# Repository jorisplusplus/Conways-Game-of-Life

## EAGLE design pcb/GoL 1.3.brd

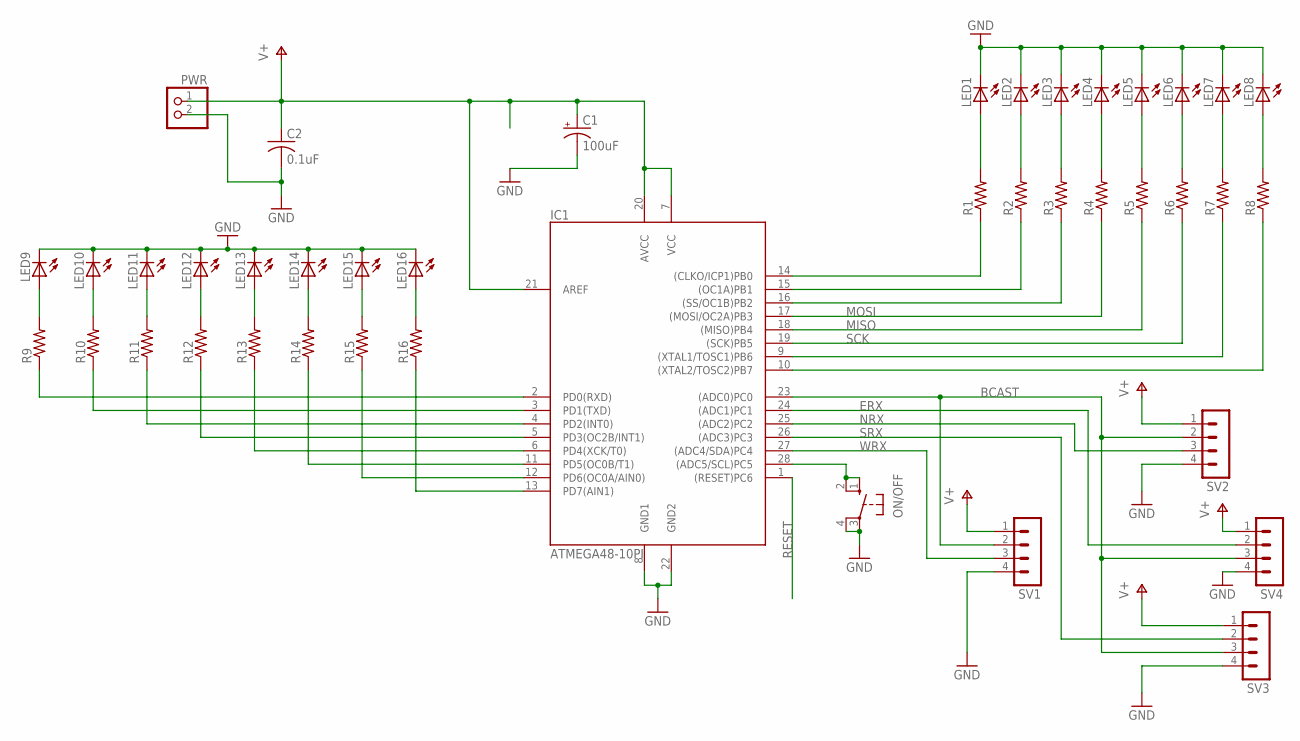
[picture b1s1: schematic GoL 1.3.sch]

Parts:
C1: 100uF; E2,5-6
C2: 0.1uF; C025-025X050
IC1: ATMEGA48-10PI; DIL28-3
LED1, LED2, LED3, LED4, LED5, LED6, LED7, LED8, LED9, LED10, LED11, LED12, LED13, LED14, LED15, LED16: LED5MMEZ; LED5MM-EZ
ON/OFF: 10-XX; B3F-10XX
PWR: PINHD-1X2; 1X02
R1, R2, R3, R4, R5, R6, R7, R8, R9, R10, R11, R12, R13, R14, R15, R16: R-US_0207/10; 0207/10
SV1, SV2, SV3, SV4: MA04-1

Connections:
BCAST: IC1.23 ((ADC0)PC0), SV1.2, SV2.2, SV3.3, SV4.3
ERX: IC1.24 ((ADC1)PC1), SV4.2
GND: C1.-, C2.2, IC1.8 (GND1), IC1.22 (GND2), LED1.K (C), LED2.K (C), LED3.K (C), LED4.K (C), LED5.K (C), LED6.K (C), LED7.K (C), LED8.K (C), LED9.K (C), LED10.K (C), LED11.K (C), LED12.K (C), LED13.K (C), LED14.K (C), LED15.K (C), LED16.K (C), ON/OFF.3, ON/OFF.4 (P1), PWR.2, SV1.4, SV2.4, SV3.4, SV4.4
MISO: IC1.18 ((MISO)PB4), R5.1
MOSI: IC1.17 ((MOSI/OC2A)PB3), R4.1
unnamed: LED1.A, R1.2
unnamed: LED2.A, R2.2
unnamed: LED3.A, R3.2
unnamed: LED4.A, R4.2
unnamed: LED5.A, R5.2
unnamed: LED6.A, R6.2
unnamed: LED7.A, R7.2
unnamed: LED8.A, R8.2
unnamed: LED9.A, R9.2
unnamed: LED10.A, R10.2
unnamed: LED11.A, R11.2
unnamed: LED12.A, R12.2
unnamed: LED13.A, R13.2
unnamed: LED14.A, R14.2
unnamed: LED15.A, R15.2
unnamed: LED16.A, R16.2
unnamed: IC1.13 (PD7(AIN1)), R16.1
unnamed: IC1.12 (PD6(OC0A/AIN0)), R15.1
unnamed: IC1.11 (PD5(OC0B/T1)), R14.1
unnamed: IC1.6 (PD4(XCK/T0)), R13.1
unnamed: IC1.5 (PD3(OC2B/INT1)), R12.1
unnamed: IC1.4 (PD2(INT0)), R11.1
unnamed: IC1.3 (PD1(TXD)), R10.1
unnamed: IC1.2 (PD0(RXD)), R9.1
unnamed: IC1.28 ((ADC5/SCL)PC5), ON/OFF.1 (S), ON/OFF.2 (S1)
unnamed: IC1.14 ((CLKO/ICP1)PB0), R1.1
unnamed: IC1.15 ((OC1A)PB1), R2.1
unnamed: IC1.16 ((SS/OC1B)PB2), R3.1
unnamed: IC1.9 ((XTAL1/TOSC1)PB6), R7.1
unnamed: IC1.10 ((XTAL2/TOSC2)PB7), R8.1
NRX: IC1.25 ((ADC2)PC2), SV2.3
RESET: IC1.1 ((RESET)PC6)
SCK: IC1.19 ((SCK)PB5), R6.1
SRX: IC1.26 ((ADC3)PC3), SV3.2
V+: C1.+, C2.1, IC1.7 (VCC), IC1.20 (AVCC), IC1.21 (AREF), PWR.1, SV1.1, SV2.1, SV3.1, SV4.1
WRX: IC1.27 ((ADC4/SDA)PC4), SV1.3

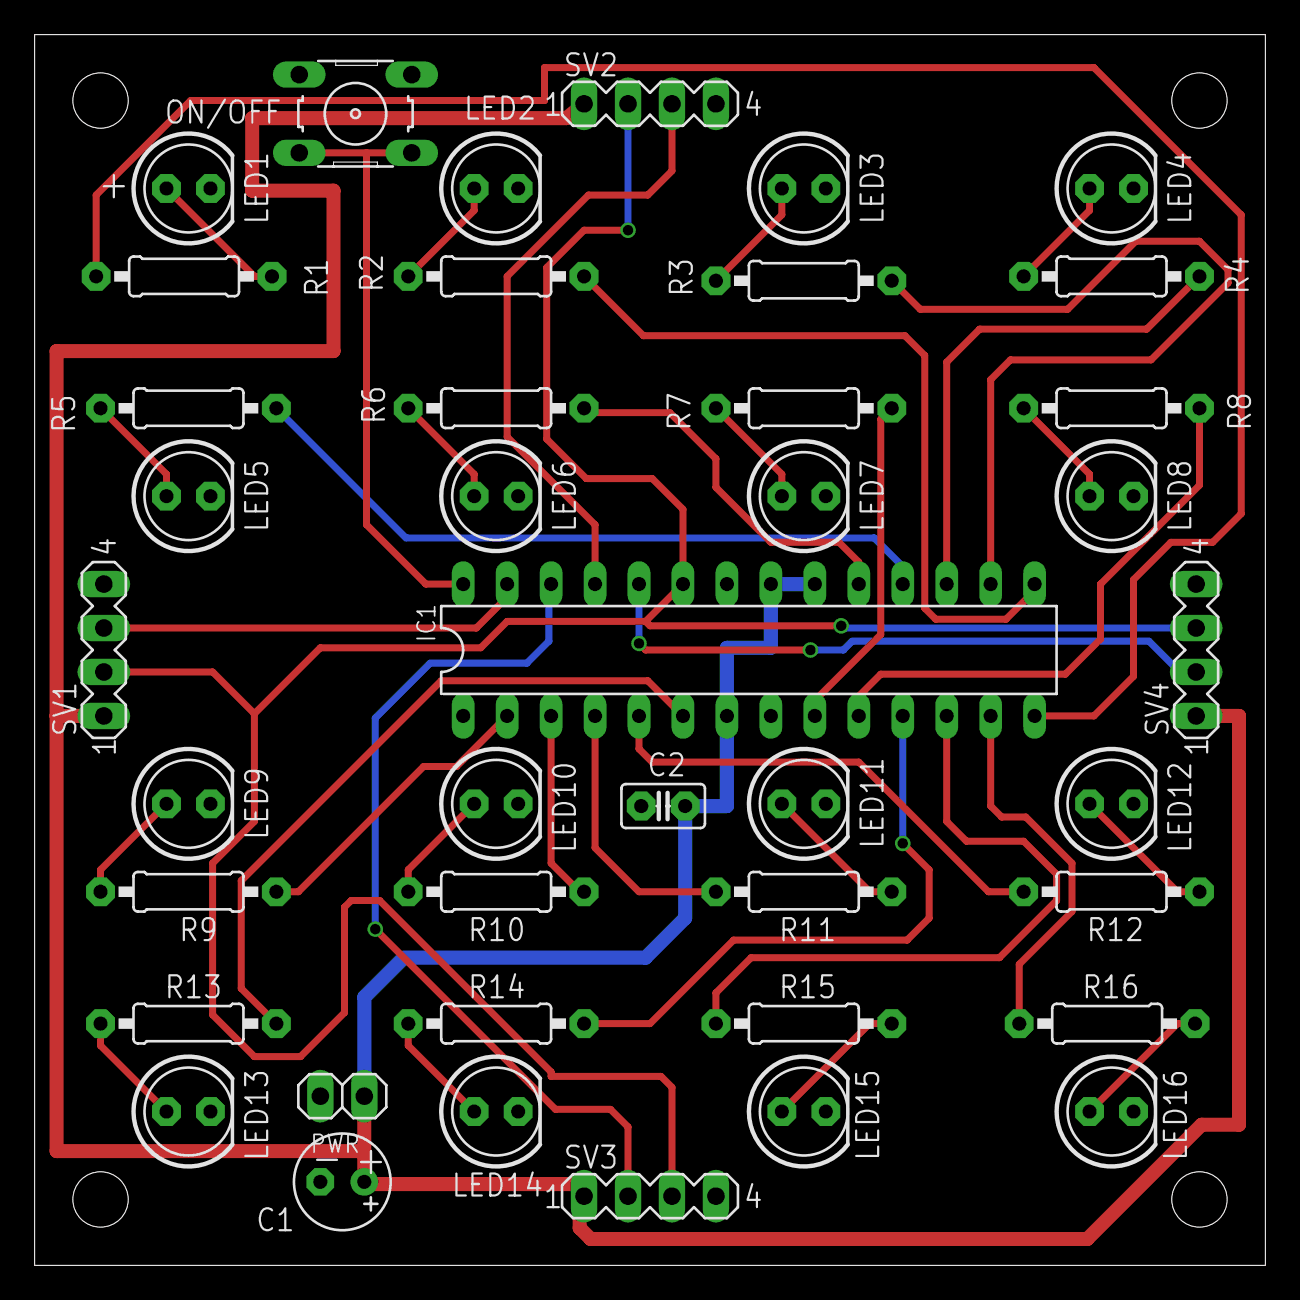
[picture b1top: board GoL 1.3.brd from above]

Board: 2 copper layers, 71.1 x 71.1 mm, 41 parts (0 on the bottom side), 40 nets.

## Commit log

2015-09-08 Removed junk
2015-09-10 Finished routing
